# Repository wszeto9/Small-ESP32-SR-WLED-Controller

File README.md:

# Small ESP32 SR-WLED Controller

A small LED controller that runs WLED-Sound Reactive. Supports 5-24V analog and addressible lights.

[Interactive BOM](https://htmlpreview.github.io/?https://raw.githubusercontent.com/wszeto9/Small-ESP32-SR-WLED-Controller/main/Documentation/ibom.html)

<h2> Features:</h2>
<ul>
<li>4 Analog Channels (Up to 3A each) for analog RGB and RGBW LED strips</li>
<li>2 Addressible Channels, level shifted to 5V to support single data line and dual data line addressible LED strips.
<li>Variable Input voltage from 5-24V (Input voltage must match the LED strip voltage)
<li>Controlled with an ESP8266 running WLED and connected over Wi-Fi</li>
<li>Panelized in a 2x2 panel of 50x50mm for minimal fabrication costs at JLCPCB</li>
<li>BOM cost is kept low at around $6 per board
</ul>
<h2>Pinout</h2>

<h2> Bring-up and Usage </h2>

- All front components should be soldered by JLCPCB.
- Flip the board and solder the ESP32 WROOM chip.
- Attach the programming device onto the mezzamine connector on the top front of the board
- Program the ESP32 with WLED
- Unplug the programming header
- Solder on lights and a power lead
- Connect to the ESP's Wi-Fi network and turn on the lights!

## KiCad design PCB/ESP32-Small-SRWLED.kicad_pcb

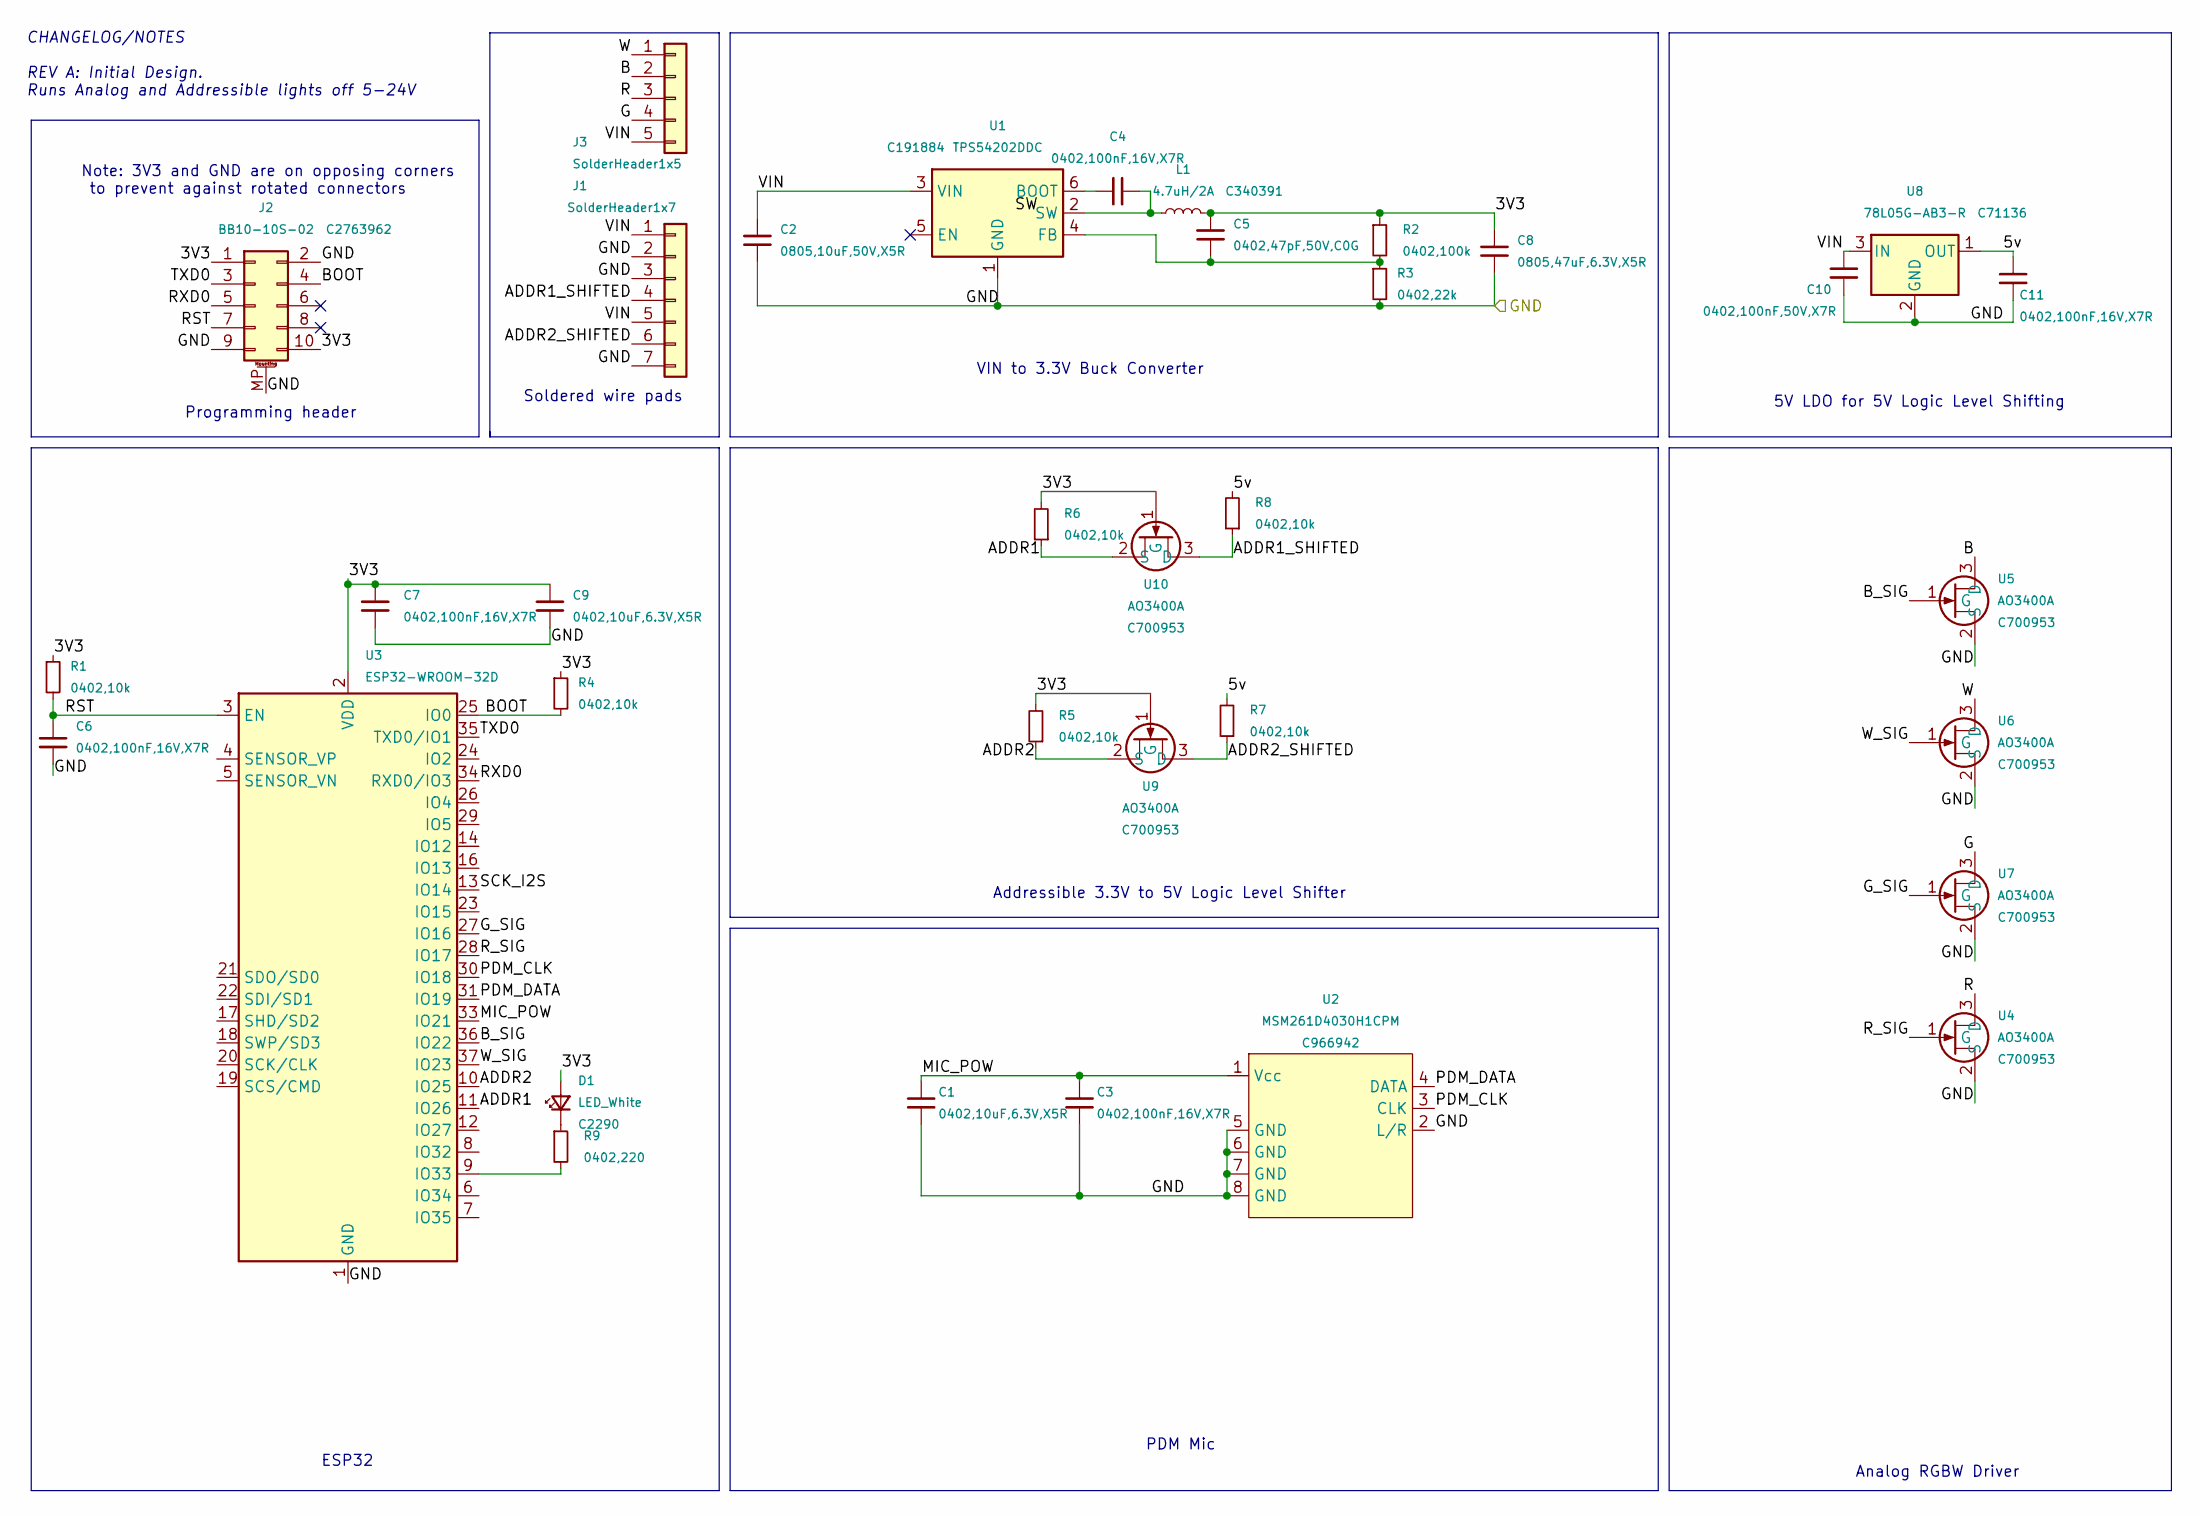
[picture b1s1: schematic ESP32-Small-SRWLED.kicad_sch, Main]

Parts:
C1, C9: 0402,10uF,6.3V,X5R; C_0402_1005Metric; MFGPN CL05A106MQ5NUNC; LCSC C15525
C2: 0805,10uF,50V,X5R; C_0805_2012Metric; MFGPN GRM21BR61H106KE43L; LCSC C440198
C3, C4, C6, C7, C11: 0402,100nF,16V,X7R; C_0402_1005Metric; MFGPN CL05B104KO5NNNC; LCSC C1525
C5: 0402,47pF,50V,C0G; C_0402_1005Metric; MFGPN 0402CG470J500NT; LCSC C1567
C8: 0805,47uF,6.3V,X5R; C_0805_2012Metric; MFGPN CL21A476MQYNNNE; LCSC C16780
C10: 0402,100nF,50V,X7R; C_0402_1005Metric; MFGPN CL05B104KB54PNC; LCSC C307331
D1: LED_White; LED_0603_1608Metric; LCSC C2290
J1: SolderHeader1x7; 1x7 wire solder pad
J2: BB10-10S-02; YXT-BB10-10S-02; LCSC C2763962
J3: SolderHeader1x5; 1x5 solder pad
L1: 4.7uH/2A; L_Wuerth_MAPI-4030; MFGPN YNR4030-4R7M; LCSC C340391
R1, R4, R5, R6, R7, R8: 0402,10k; R_0402_1005Metric; MFGPN 0402WGF1002TCE; LCSC C25744
R2: 0402,100k; R_0402_1005Metric; MFGPN 0402WGF1003TCE; LCSC C25741
R3: 0402,22k; R_0402_1005Metric; MFGPN 0402WGF2202TCE; LCSC C25768
R9: 0402,220; R_0402_1005Metric; MFGPN 0402WGF2200TCE; LCSC C25091
U1: TPS54202DDC; SOT-23-6; MFGPN TPS54202DDCR; LCSC C191884
U2: MSM261D4030H1CPM; LCSC C966942
U3: ESP32-WROOM-32D; ESP32-WROOM-32; LCSC C473005
U4, U5, U6, U7, U9, U10: AO3400A; SOT-23; LCSC C700953
U8: 78L05G-AB3-R; SOT-89-3; LCSC C71136

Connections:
/3V3: C5.1, C7.1, C8.1, C9.1, D1.2 (A), J2.1, J2.10, L1.2, R1.1, R2.1, R4.1, R5.2, R6.2, U3.2 (VDD), U9.1 (G), U10.1 (G)
/5v: C11.1, R7.2, R8.2, U8.1 (OUT)
/ADDR1: R6.1, U3.11 (IO26), U10.2 (S)
/ADDR1_SHIFTED: J1.4, R8.1, U10.3 (D)
/ADDR2: R5.1, U3.10 (IO25), U9.2 (S)
/ADDR2_SHIFTED: J1.6, R7.1, U9.3 (D)
/B: J3.2, U5.3 (D)
/BOOT: J2.4, R4.2, U3.25 (IO0)
/B_SIG: U3.36 (IO22), U5.1 (G)
/G: J3.4, U7.3 (D)
/GND: C1.2, C2.2, C3.2, C6.2, C7.2, C8.2, C9.2, C10.2, C11.2, J1.2, J1.3, J1.7, J2.2, J2.9, J2.MP (MountPin), R3.2, U1.1 (GND), U2.2 (L/R), U2.5 (GND), U2.6 (GND), U2.7 (GND), U2.8 (GND), U3.1 (GND), U3.15 (GND), U3.38 (GND), U3.39 (GND), U4.2 (S), U5.2 (S), U6.2 (S), U7.2 (S), U8.2 (GND)
/G_SIG: U3.27 (IO16), U7.1 (G)
/MIC_POW: C1.1, C3.1, U2.1 (Vcc), U3.33 (IO21)
/PDM_CLK: U2.3 (CLK), U3.30 (IO18)
/PDM_DATA: U2.4 (DATA), U3.31 (IO19)
/R: J3.3, U4.3 (D)
/RST: C6.1, J2.7, R1.2, U3.3 (EN)
/RXD0: J2.5, U3.34 (RXD0/IO3)
/R_SIG: U3.28 (IO17), U4.1 (G)
/SCK_I2S: U3.13 (IO14)
/TXD0: J2.3, U3.35 (TXD0/IO1)
/VIN: C2.1, C10.1, J1.1, J1.5, J3.5, U1.3 (VIN), U8.3 (IN)
/W: J3.1, U6.3 (D)
/W_SIG: U3.37 (IO23), U6.1 (G)
unnamed: C4.1, U1.6 (BOOT)
unnamed: C4.2, L1.1, U1.2 (SW)
unnamed: C5.2, R2.2, R3.1, U1.4 (FB)
unnamed: D1.1 (K), R9.1
unnamed: R9.2, U3.9 (IO33)

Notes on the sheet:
5V LDO for 5V Logic Level Shifting
VIN to 3.3V Buck Converter
PDM Mic
Analog RGBW Driver
Programming header
Addressible 3.3V to 5V Logic Level Shifter
Soldered wire pads
ESP32
Note: 3V3 and GND are on opposing corners to prevent against rotated connectors
CHANGELOG/NOTES REV A: Initial Design. Runs Analog and Addressible lights off 5-24V

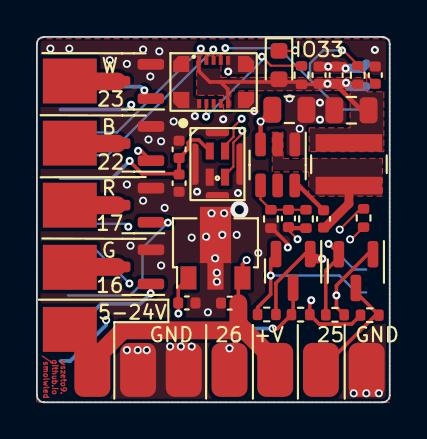
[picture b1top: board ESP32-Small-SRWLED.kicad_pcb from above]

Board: 4 copper layers, 19.6 x 20.3 mm, 35 parts (1 on the bottom side), 28 nets.

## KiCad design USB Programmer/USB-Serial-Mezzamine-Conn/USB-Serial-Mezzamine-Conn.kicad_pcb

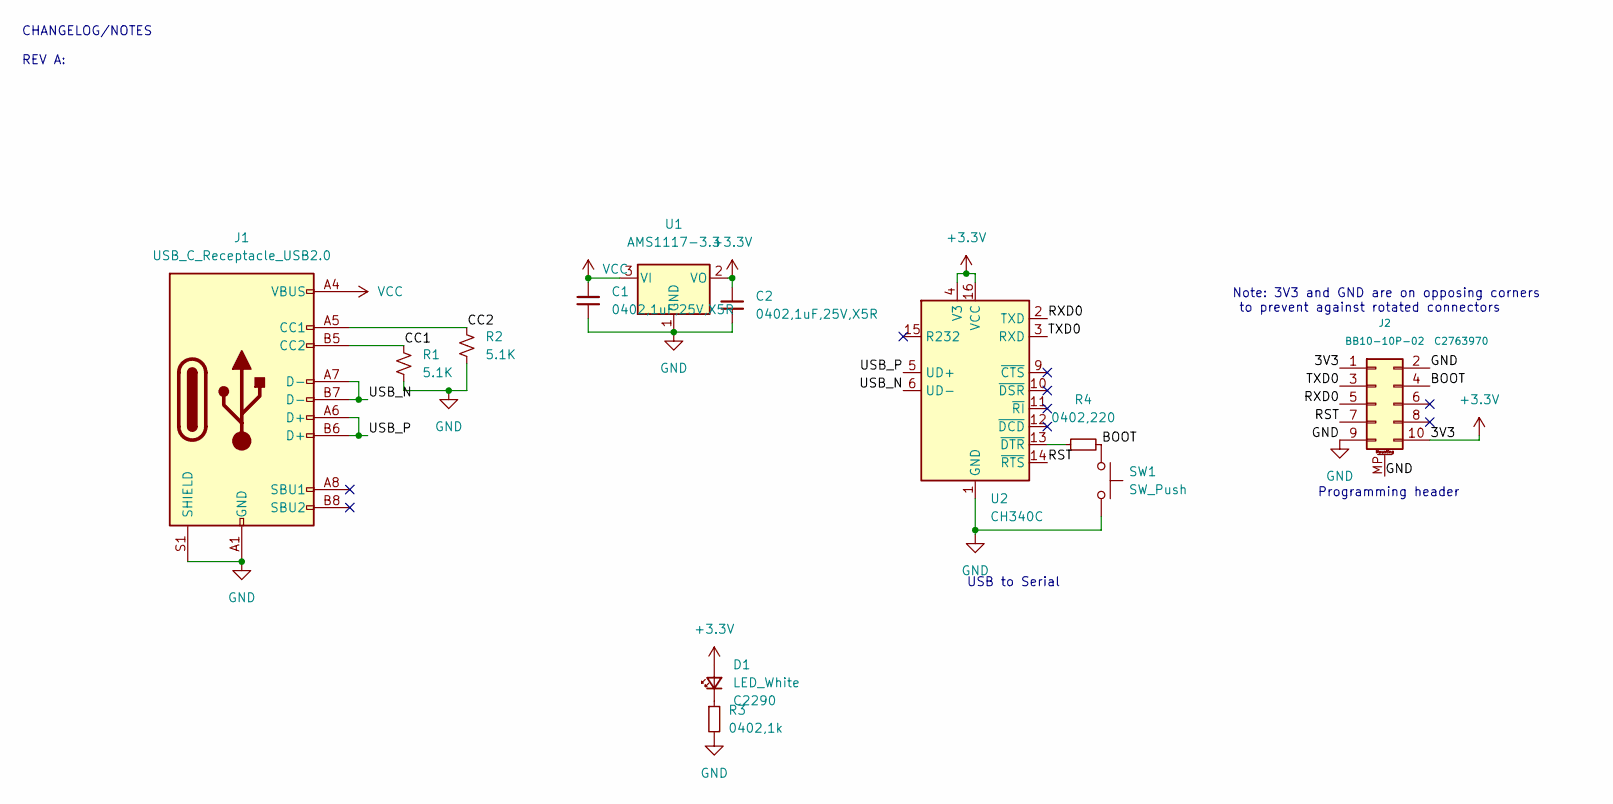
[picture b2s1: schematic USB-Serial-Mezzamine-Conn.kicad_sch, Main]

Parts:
C1, C2: 0402,1uF,25V,X5R; C_0402_1005Metric; MFGPN CL05A105KA5NQNC; LCSC C52923
D1: LED_White; LED_0603_1608Metric; LCSC C2290
J1: USB_C_Receptacle_USB2.0; USB_C_Receptacle_Palconn_UTC16-G; LCSC Part Number C165948
J2: BB10-10P-02; YXT-BB10-10P-02; LCSC C2763970
R1, R2: 5.1K; R_0402_1005Metric; LCSC Part Number C25905
R3: 0402,1k; R_0402_1005Metric; MFGPN 0402WGF1001TCE; LCSC C11702
R4: 0402,220; R_0402_1005Metric; MFGPN 0402WGF2200TCE; LCSC C25091
SW1: SW_Push; SW_PUSH_6mm
U1: AMS1117-3.3; SOT-223-3_TabPin2
U2: CH340C; SOIC-16_3.9x9.9mm_P1.27mm; LCSC Part Number C84681

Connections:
+3V3: C2.1, D1.2 (A), J2.1, J2.10, U1.2 (VO), U2.4 (V3), U2.16 (VCC)
/BOOT: J2.4, R4.2, SW1.1
/CC1: J1.B5 (CC2), R1.1
/CC2: J1.A5 (CC1), R2.1
/RST: J2.7, U2.14 (~RTS)
/RXD0: J2.5, U2.2 (TXD)
/TXD0: J2.3, U2.3 (RXD)
/USB_N: J1.A7 (D-), J1.B7 (D-), U2.6 (UD-)
/USB_P: J1.A6 (D+), J1.B6 (D+), U2.5 (UD+)
GND: C1.2, C2.2, J1.A1 (GND), J1.A12 (GND), J1.B1 (GND), J1.B12 (GND), J1.S1 (SHIELD), J2.2, J2.9, J2.MP (MountPin), R1.2, R2.2, R3.2, SW1.2, U1.1 (GND), U2.1 (GND)
unnamed: D1.1 (K), R3.1
unnamed: R4.1, U2.13 (~DTR)
VCC: C1.1, J1.A4 (VBUS), J1.A9 (VBUS), J1.B4 (VBUS), J1.B9 (VBUS), U1.3 (VI)

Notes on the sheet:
Programming header
Note: 3V3 and GND are on opposing corners to prevent against rotated connectors
USB to Serial
CHANGELOG/NOTES REV A:

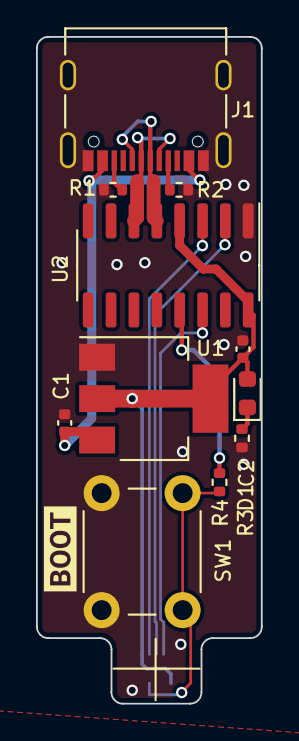
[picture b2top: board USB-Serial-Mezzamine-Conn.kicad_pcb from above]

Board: 2 copper layers, 12.5 x 37.0 mm, 13 parts (1 on the bottom side), 13 nets.

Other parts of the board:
kibuzzard-63EDCBFB: G***; kibuzzard-63EDCBFB

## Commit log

2023-02-14 Routed components
2023-02-14 edited website link
2023-02-14 changed file dir
2023-02-27 sent to fab
2023-02-27 Added scope shots of 3.3V ripple voltage
2023-04-01 moved bom and step to documentation
2023-07-22 Adding documentation
